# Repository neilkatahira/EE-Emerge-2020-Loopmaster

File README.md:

# Loop Master

[Loopmaster](https://neilkatahira.github.io/EE-Emerge-2020-Loopmaster/) is a musical project created by a team of UC Davis [EE-Emerge](https://www.ece.ucdavis.edu/ieee/home/ee-emerge/) (EEC 105ABC) students. This project allows you to create your own musical melodies or riffs, regardless of skill level or knowledge. Three custom "instruments" interface together to output notes based on the user's selections.

## Table of Contents

1. [About the Project](#about-the-project)
2. [Project Status](#project-status)
3. [Getting Started](#getting-started)
    1. [Dependencies](#dependencies)
    1. [Building](#building)
4. [How to Get Help](#how-to-get-help)
5. [Further Reading](#further-reading)
6. [Authors](#authors)
7. [Acknowledgements](#acknowledgements)

# About the Project

Three instruments (Drumpad, Computer Vision, and Footpad) work with selections specified in a MATLAB GUI. A BeagleBone Black and a Bela Cape is utilized to process user inputs and output different notes.
The Drumpad works like a traditional MIDI pad, where each of the twelve buttons are mapped to notes that relate to a selection of instruments. The Computer Vision maps different notes to select areas in a camera's view and outputs sound when a trigger is visible. The Footpad takes input from a user's feet and manipulates the sounds created by the Camera Vision and Drumpad.

# Project Status

Final assembly and code refinement.

# Getting Started

This repository can be downloaded [here](https://github.com/neilkatahira/EE-Emerge-2020-Loopmaster/archive/master.zip), or cloned by:
```
git clone https://github.com/neilkatahira/EE-Emerge-2020-Loopmaster
```

## Dependencies

#### Software
[Energia](https://energia.nu/)  
Energia is required for the Drumpad and Footpad to compile and run the .ino files.

[OpenMV IDE](https://openmv.io/pages/download)  
The OpenMV IDE is used for all of the programming of the H7 Camera.

[PureData](https://github.com/BelaPlatform/Bela/wiki/Getting-started-with-Bela)  
The Bela IDE is used for the majority of the workflow for the Beaglebone + Bela.

#### Hardware & Model Creation
[Altium](https://www.altium.com/) was used for most PCB creation.  
[Eagle](https://www.autodesk.com/products/eagle/overview) was used to make the CameraPCB.  
[Fusion 360](https://www.autodesk.com/products/fusion-360/overview) was used for the creation of enclosures and other mechanical files.  
[Cura](https://ultimaker.com/software/ultimaker-cura) was used as our main slicer for 3D printing. The UC Davis ESDC's Ultimaker's and personal Ender 3 Pro's were used for fabrication.  

## Building

PCB and enclosure files will be located in their respective subdirectories. These were fabricated either with a 3D printer, a laser cutter, or table saw.

Software for the instruments will have to be compiled and loaded into their respective MCU's either in the Puredata IDE or Energia.

# How to Get Help

You can request any changes by making a [pull request](https://github.com/neilkatahira/EE-Emerge-2020-Loopmaster/pulls) or opening an issue.

# Further Reading
* [Airdrum](https://hackaday.com/2019/11/15/finally-your-air-drumming-has-an-outlet/)
* [Foot Piano](https://www.instructables.com/id/Build-a-Big-Piano/)

# Authors

* [Benjamin Moore](https://github.com/mooreben34)
* [Conrad Rowling](https://github.com/Conrad-Rowling)
* [Neil Katahira](https://github.com/neilkatahira)
* [Jocelyn Park](https://github.com/spectivePer)
* [Isabelle Asistin](https://github.com/ijasistin)
* [Varsha Senthil](https://github.com/varshaaaaa)
* [Tyler Kelley](https://github.com/tfkelley)
* [Ryan Ma](https://github.com/RyanMa1)
* [Devon Liu](https://github.com/dvnliu)
* [Sean Alling](https://www.ece.ucdavis.edu/blog/alling-sean/)
* [Professor Andre Knoesen](https://faculty.engineering.ucdavis.edu/knoesen/)

# Acknowledgments

Thanks to Texas Instruments for sponsoring EE-Emerge, along with Sean Alling and Dr. Andre Knoesen. We would not have gotten this far without their help and support.

Huge shout out to Alessandro Verdiesen and Luuk van Kuijk with the original idea and inspiration of the [Airdrum](https://hackaday.com/2019/11/15/finally-your-air-drumming-has-an-outlet/) and the whole project.

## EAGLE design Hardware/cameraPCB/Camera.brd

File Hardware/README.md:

# Hardware Designs

Our system was fairly robust, and we needed quite a few board to complete it. The backbone of our hardware was based on the following boards:

[BeagleBoneBlack](https://beagleboard.org/black)  
[Bela Cape](https://beagleboard.org/p/112305/bela-low-latency-audio-sensor-cape-for-pocketbeagle-1615e0)  
[MSP430G2 LaunchPad](http://www.ti.com/tool/MSP-EXP430G2)  
[OpenMV H7](https://openmv.io/products/openmv-cam-h7)  
Capsense Buttons
Power Supply
Batteries

Once we proved functionality, we designed our own circuitboards to improve the connections as well as size parameters of the pre-fabricated boards.

## Table of Contents

1. [Board Selection](#board-selection)  
   - [BeagleBoneBlack/BelaCape](#beagleboneblack/belaCape)  
   - [OpenMV H7](#openMv-h7)  
   - [MSP430](#msp430)  
   - [Xbee Module](#xbee-module)  
   - [Miscellaneous](#miscellaneous)  
2. [Custom Boards](#custom-boards)  
   - [Beagle Cape Cape](#beagle-cape-cape)  
   - [Drumpad/Keypad](#drumpad/keyboard)  
   - [Camera Cape](#camer-cape)  
   - [Button Wiring Harness](#button-wiring-harness)  
    
## Board Selection

### BeagleBoneBlack/BelaCape  
The base of project was creating music, which meant making quality sounds at a responsive rate. This meant we needed low latency, as low as we could get it within budget! We built our system around the [BeagleBoneBlack](https://beagleboard.org/black) and [Bela Cape](https://beagleboard.org/p/112305/bela-low-latency-audio-sensor-cape-for-pocketbeagle-1615e0) which would combined process the input of instruments and output fast and quality sound.

### OpenMV H7  
We chose the OpenMV H7 because it is a relatively cheap, low power camera, that has loads of documentation and is very easy to work with. It has more than enough processing power to accomplish our tasks, as well as an IDE that uses python. 

### MSP430  
We chose to use these boards because everyone on our team had experience working with them, they are easy to use, and use an IDE that is almost identical to the Arduino IDE. They were also provided to us in launchboard form by [Texas Instruments](http://www.ti.com/) which vastly accelerated the project developement phase. - BIG THANKS! 

### Xbee Module  
The Xbee module was a final implementation on the project to provide wireless communication. These modules are incredibly easy to use, and are very small. They are an excellent choice to provide wireless serial communication.

### Miscellaneous  
Power Supply, Batteries, Voltage Regulators and Capsense tech

## Custom Boards  
We used several Integrated Processors in the development of our project. In most cases we used development boards, jumperwires and breadboards which allowed easy connections to test functionality. We started with but the finished project was something professional, so we designed our own boards to house the integrated chips we were programming ([MSP430](http://www.ti.com/microcontrollers/msp430-ultra-low-power-mcus/overview.html)'s) as well as capes for the pre-fabricated boards we were using ([OpenMV H7](https://openmv.io/products/openmv-cam-h7) and [BeagleBoneBlack](https://beagleboard.org/black)/[Bela Cape](https://beagleboard.org/p/112305/bela-low-latency-audio-sensor-cape-for-pocketbeagle-1615e0)).This allowed us to create more stable connection points, remove unnecessary functions, and create room for new functions (Xbee wireless Communication).

### Beagle Cape Cape  
We designed a board that would connect to the breakout pins of the BeagleBoneBlack. It replaced the GPIO pinnouts with screw terminal connections for the required Serial ports and 3.3V rail. It also laid a footprint for a permanent addition of an Xbee module.

### Drumpad/Keypad  
We developed one board that would function for both the Drumpad as well as the foot keyboard. It housed a MSP430 and provided ample room for the GPIO pins that were needed in instrument function.(MORE DETAILS) THe board replaced the GPIO pin out with screw terminals for better permanent connections. The board was also made with a footprint for an Xbee module to be soldered on.

### Camera Cape  
The most simple board we designed for the OpenMV camera module, it took the pinouts we needed from the development board and implemented screw terminals for better permanent connections.

### Drumpad Wiring Harness  
We designed a board that simplified the wiring harness for 12 capacitive sense buttons. Each button required an op-amp to forward the button data as well as provide power to LEDs. We developed a board that made this complex wiring array compact and easy to trouble shoot. This allowed us to reduce the overall size requirements of the Drumpad Enclosure as well as reducing EM noise within the enclosure.

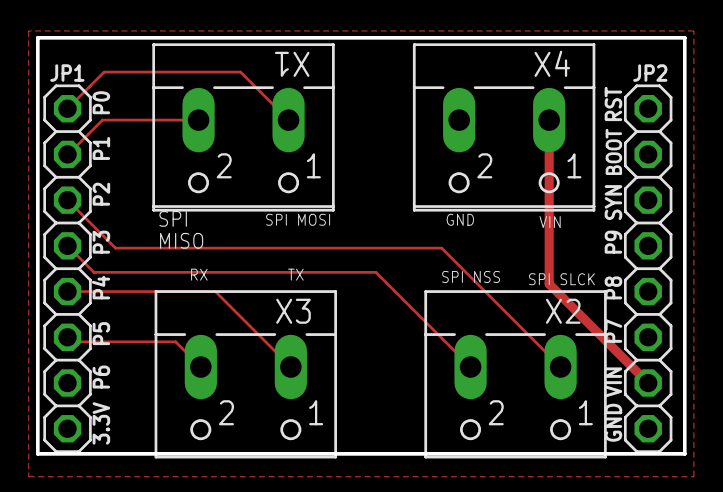
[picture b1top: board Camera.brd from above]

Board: 2 copper layers, 35.9 x 23.1 mm, 6 parts (0 on the bottom side), 8 nets.

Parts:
JP1, JP2: 1X08
X1, X2, X3, X4: W237-102

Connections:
GND: JP2.8, X4.2
I2C2_SCL: JP1.5, X3.1
I2C2_SDA: JP1.6, X3.2
SPI2_MISO: JP1.2, X1.2
SPI2_MOSI: JP1.1, X1.1
SPI2_NSS: JP1.4, X2.2
SPI2_SCLK: JP1.3, X2.1
VIN: JP2.7, X4.1

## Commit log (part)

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2020-04-04 Create fill
2020-04-10 New Info
2020-04-10 Links and typos
2020-04-10 Project Status
2020-04-13 Updating gh-pages link and other links
2020-04-13 Docs folder for gh-pages
2020-04-16 SingleSendDrumpad.ino
    sends only when the state changes
2020-04-23 Updated author links
2020-04-24 Update website readme and drumpad stl
2020-04-24 Documentation files for Drumpad
2020-04-24 Fix formatting
2020-04-24 Reorganization
2020-04-24 Typo and minor fixes
2020-04-24 Sub categories for dependencies
2020-04-24 Fix software
2020-04-24 Markdown fix
2020-04-24 Software fix
2020-04-26 MATLAB GUI & corresponding Arduino files
2020-04-26 GUI README
2020-04-28 Screw hole size changes
2020-04-28 Increased standoff sizes + fixed cable hole
2020-04-29 Added supports for mounting holes
2020-05-06 Create GitHubPages
2020-05-12 Create placeholder
2020-05-12 Drumpad LED PCB v2
    New revision of the Drumpad LED PCB. Includes Altium files, gerbers, pictures and schematic PDF.
2020-05-12 Folder name change
2020-05-12 Update for LEDPCB v2
2020-05-12 Reoriented standoffs for LED PCB, resized hole sizes for mainboard
2020-05-15 Changed screw size for mainboard
    Screw size of mainboard from M2 to M2.5
2020-05-22 Finalized serial codes for GUI
2020-05-23 Readme update
2020-05-23 replaced with the folder
2020-05-23 renaming
2020-05-23 Set theme jekyll-theme-cayman
2020-05-24 Website update
2020-05-24 Remove skip banner
2020-05-24 Change theme color
2020-05-24 Styles
2020-05-24 SCSS
2020-05-24 Added page
2020-05-24 Site Update
2020-05-24 Preliminary Drum pad page info
2020-05-24 Fix github and download links to target new tab
2020-05-24 Team update
2020-05-24 Move authors
2020-05-24 Added info
2020-05-24 Remove redundancy with description
2020-05-24 Page updates for description
2020-05-24 Rename _data/nav.html to doc/_data/nav.html
2020-05-24 Rename doc/_data/nav.html to docs/_data/nav.html
2020-05-24 Rename _data/nav.yml to docs/_data/nav.yml
2020-05-24 Create acknowledgements
2020-05-24 Rename acknowledgements to acknowledgements.md
2020-05-24 NewCode style
2020-05-24 Updated links
2020-05-24 Updated footer links to open to new tab
2020-05-24 Markdown formatting fix
2020-05-24 Camera vision to computer
2020-05-24 Removed Xbee board standoffs
2020-05-24 Create pics
2020-05-27 Pictures
2020-05-27 Fix name
2020-05-27 Upload pictures
2020-05-27 Page update
2020-05-27 Add puredata picture
2020-05-27 Formatting and resize
2020-05-27 Page updates
2020-05-27 Wording
2020-05-27 Revert
2020-05-29 Remove chill
2020-05-29 updating pages
2020-05-29 troubleshooting pngs
2020-05-29 camera vision
2020-05-29 new photos
2020-05-29 photos
2020-05-29 change size
2020-05-29 changing Photos
2020-05-29 pics
2020-05-29 youtube maybe
2020-05-29 edits
2020-05-29 pngs not jpgs
2020-05-29 centering images
2020-05-29 new gif added
2020-05-31 Jocelyn
2020-05-31 Update links
2020-05-31 Formatting
2020-06-20 Create LICENSE
2020-06-20 remove old dependencies
